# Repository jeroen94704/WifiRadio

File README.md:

WifiRadio
=========

Introduction
------------

This is the software part of my version of the ubiquitous wifi radio projects. There are many similar builds to be found online, 
and they all use a cheap router as an internet streaming radio, usually running MPD (http://mpd.wikia.com/wiki/Music_Player_Daemon_Wiki) 
to play the music. My build borrows heavily from the radio project by Jeff Keyzer, A.K.A. MightyOhm. He documented the process he 
went through in great detail on his blog, at http://mightyohm.com/blog/2008/10/building-a-wifi-radio-part-1-introduction/

In addition, I also owe a great deal to the SparkFun tutorial "Beginning embedded electronics", which can be found at 
http://www.sparkfun.com/tutorials/57

Contents
--------

The repository contains the following:

* C-code, to be compiled and programmed onto a suitable AVR microcontroller
* A perl script, which runs on the router
* Eagle schematics and board files of the electronics

Features
--------

The firmware+perl script system has the following features:

* Load a predefined playlist containing a set of internet streams
* Browse and play from an MP3 collection located on a network share
* Show currently playing information, including progress in the current track, title/artist info and playlist info

Usage
-----

The player is controlled using a 6-button keypad, with up/down/left/right/enter keys, and a mode switch key. The player starts in radio mode, 
playing the predefined set of internet streams. Pressing the mode switch key will start the MP3 browser mode, and shows the first few MP3 directories 
(in my case, artists). The browser is fully file based, so ID3 tags inside the MP3's are not interpreted. Use up/down to move through the list, press 
"right" to enter a directory, and show what's inside. Press "left" to go up one directory level. Press "enter" to play the currently selected item. If
this is a directory, everything inside that directory and its subdirectories will be played. Pressing the mode switch button again will reload and play
the predefined internet streams once more.

While playing, left/right let you move through the playlist, while up/down controls the volume (not shown on the display).
	
Technical details
-----------------
	
### C-Code

The code was built using the WinAVR suite of tools. You can use the included makefile to build your own binary, which includes targets to set the fuses and program the MPU.

### Perl script

This is a firm departure from Jeff's build, which uses bash scripting to do all the router-side processing. Since I need fairly elaborate two-way communication, involving
a lot of string parsing, using Perl with its built-in regex support was a logical move. The code is a bit dirty in the way it handles 2-way requests (e.g. When the AVR 
asks for a list of tracks). These requests involve receiving a message, processing it, and sending a result back to the AVR. The script forks at startup, so the receiving
and sending parts run in different processes.

When a results needs to be returned to the AVR, the receiver process writes a file containing the response. The sender process detects the existance if this file, reads it, 
sends the data over the serial line, and removes the file. 

More investigation is needed to determine whether the fork is actually necessary. An alternative would be to move to C, and use a proper multithreading approach, but I've 
cracked my skull against setting up an OpenWrt toolchain in the past, and have no immediate desire to attempt this again, also since the current implementation works just fine.

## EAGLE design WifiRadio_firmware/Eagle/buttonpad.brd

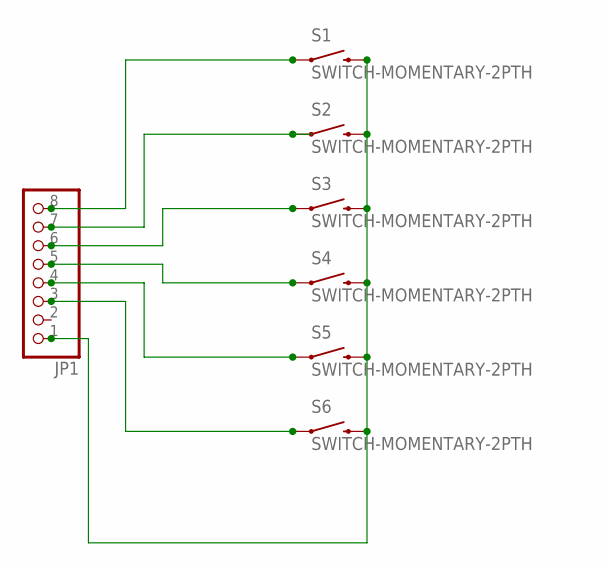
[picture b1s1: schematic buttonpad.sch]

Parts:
JP1: PINHD-1X8; 1X08
S1, S2, S3, S4, S5, S6: SWITCH-MOMENTARY-2PTH; TACTILE-PTH

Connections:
GND: JP1.1, S1.3 (2), S2.3 (2), S3.3 (2), S4.3 (2), S5.3 (2), S6.3 (2)
unnamed: JP1.8, S1.1
unnamed: JP1.6, S3.1
unnamed: JP1.3, S6.1
unnamed: JP1.7, S2.1
unnamed: JP1.5, S4.1
unnamed: JP1.4, S5.1

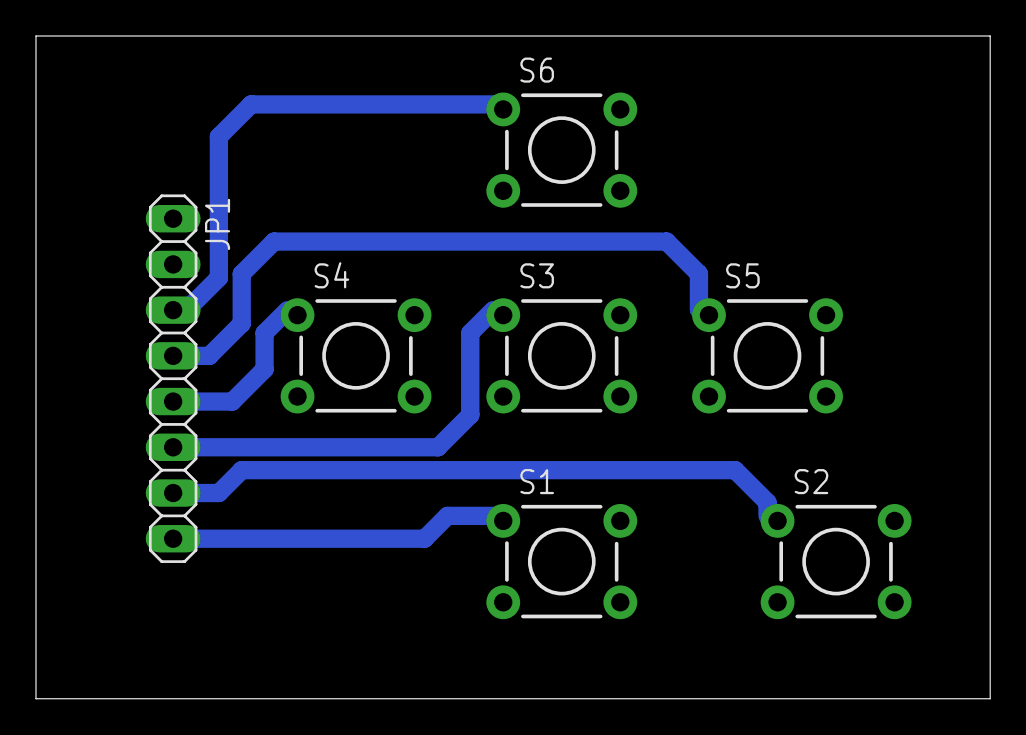
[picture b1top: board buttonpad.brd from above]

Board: 2 copper layers, 53.0 x 36.8 mm, 7 parts (0 on the bottom side), 7 nets.

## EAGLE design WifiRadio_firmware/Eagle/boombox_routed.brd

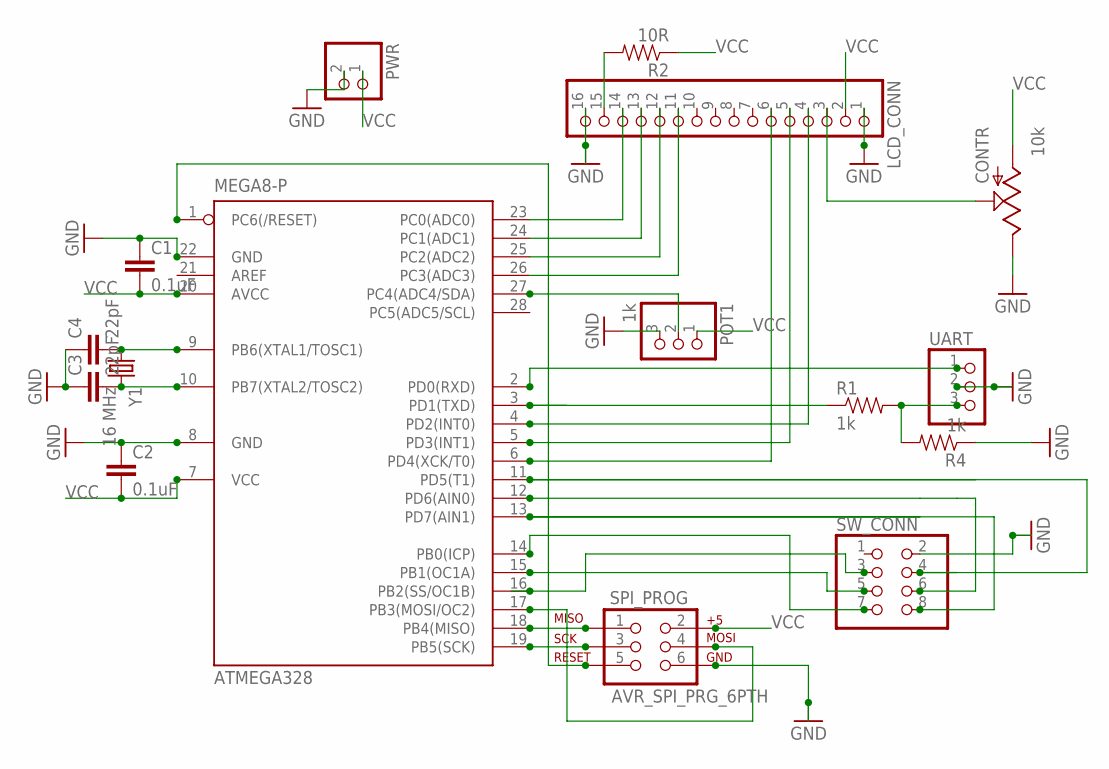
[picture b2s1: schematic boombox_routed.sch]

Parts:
ATMEGA328: MEGA8-P; DIL28-3
C1, C2: 0.1uF; C2.5-2
C3, C4: 22pF; C2.5-2
CONTR: 10k; 3362U
LCD_CONN: PINHD-1X16; 1X16
POT1: 1k; 1X03
PWR: PINHD-1X2; 1X02
R1, R4: 1k; AXIAL-0.4
R2: 10R; AXIAL-0.4
SPI_PROG: AVR_SPI_PRG_6PTH; 2X3
SW_CONN: PINHD-2X4; 2X04
UART: PINHD-1X3; 1X03
Y1: 16 MHz; HC49US

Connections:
GND: ATMEGA328.8 (GND), ATMEGA328.22 (GND), C1.1, C2.1, C3.1, C4.1, CONTR.P$1 (E), LCD_CONN.1, LCD_CONN.16, POT1.3, PWR.2, R4.P$1 (1), SPI_PROG.6, SW_CONN.1, SW_CONN.2, UART.2; also elsewhere on the board
unnamed: ATMEGA328.10 (PB7(XTAL2/TOSC2)), C3.2, Y1.2
unnamed: ATMEGA328.9 (PB6(XTAL1/TOSC1)), C4.2, Y1.1
unnamed: CONTR.P$2 (S), LCD_CONN.3
unnamed: ATMEGA328.3 (PD1(TXD)), R1.P$1 (1)
unnamed: R1.P$2 (2), R4.P$2 (2), UART.3
unnamed: ATMEGA328.2 (PD0(RXD)), UART.1
unnamed: ATMEGA328.4 (PD2(INT0)), LCD_CONN.4
unnamed: ATMEGA328.5 (PD3(INT1)), LCD_CONN.5
unnamed: ATMEGA328.6 (PD4(XCK/T0)), LCD_CONN.6
unnamed: LCD_CONN.15, R2.P$2 (2)
unnamed: ATMEGA328.23 (PC0(ADC0)), LCD_CONN.14
unnamed: ATMEGA328.24 (PC1(ADC1)), LCD_CONN.13
unnamed: ATMEGA328.25 (PC2(ADC2)), LCD_CONN.12
unnamed: ATMEGA328.26 (PC3(ADC3)), LCD_CONN.11
unnamed: ATMEGA328.19 (PB5(SCK)), SPI_PROG.3
unnamed: ATMEGA328.18 (PB4(MISO)), SPI_PROG.1
unnamed: ATMEGA328.17 (PB3(MOSI/OC2)), SPI_PROG.4
unnamed: ATMEGA328.14 (PB0(ICP)), SW_CONN.7
unnamed: ATMEGA328.27 (PC4(ADC4/SDA)), POT1.2
unnamed: ATMEGA328.15 (PB1(OC1A)), SW_CONN.5
unnamed: ATMEGA328.12 (PD6(AIN0)), SW_CONN.6
unnamed: ATMEGA328.13 (PD7(AIN1)), SW_CONN.8
unnamed: ATMEGA328.11 (PD5(T1)), SW_CONN.4
unnamed: ATMEGA328.16 (PB2(SS/OC1B)), SW_CONN.3
unnamed: ATMEGA328.1 (PC6(/RESET)), SPI_PROG.5
VCC: ATMEGA328.7 (VCC), ATMEGA328.20 (AVCC), C1.2, C2.2, CONTR.P$3 (A), LCD_CONN.2, POT1.1, PWR.1, R2.P$1 (1), SPI_PROG.2; also elsewhere on the board

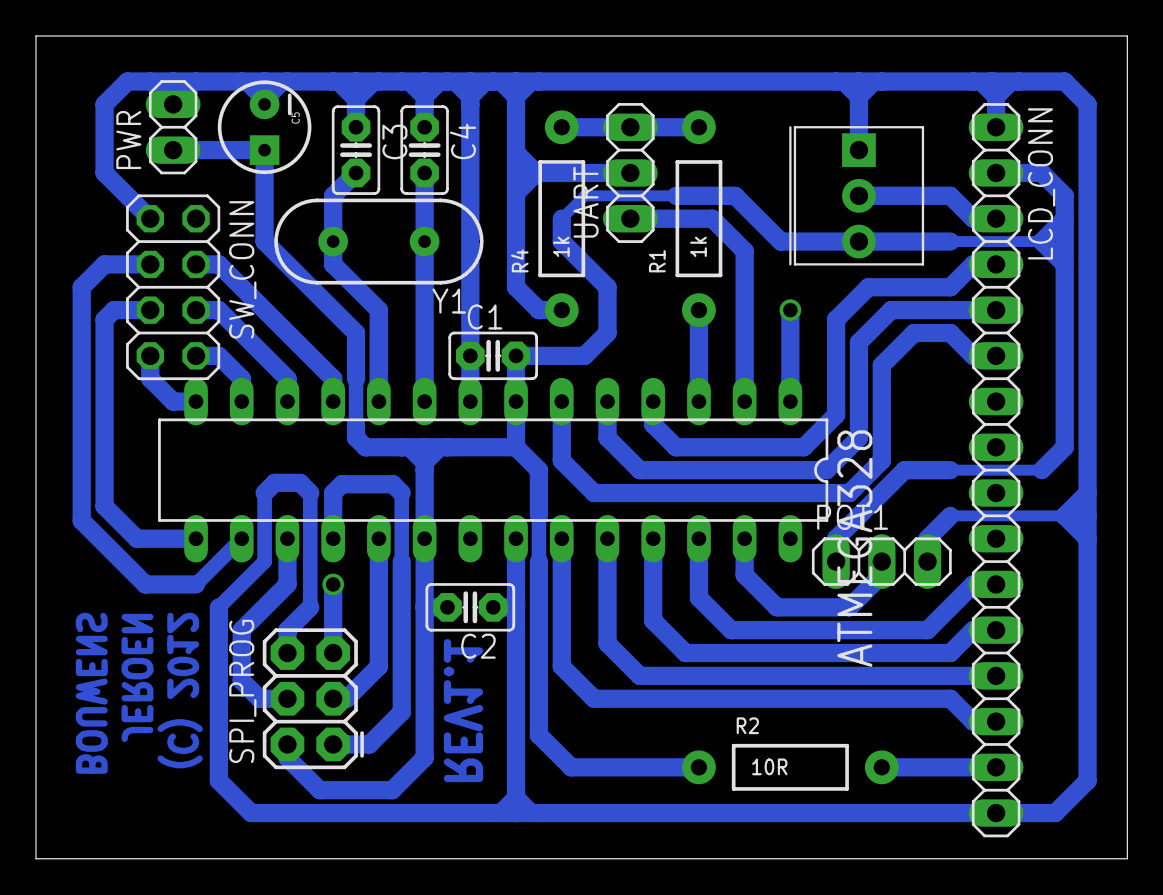
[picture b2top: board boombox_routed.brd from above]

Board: 2 copper layers, 60.6 x 45.7 mm, 17 parts (0 on the bottom side), 27 nets.

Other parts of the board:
C5: 10uF; CPOL-RADIAL-10UF-25V

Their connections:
GND: C5.2; also elsewhere on the board
VCC: C5.1; also elsewhere on the board

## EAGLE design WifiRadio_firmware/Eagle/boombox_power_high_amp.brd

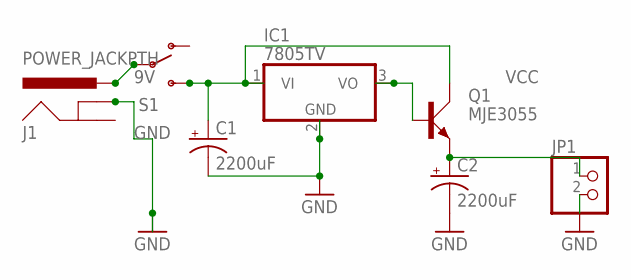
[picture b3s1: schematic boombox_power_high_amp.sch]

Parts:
C1, C2: 2200uF; CPOL-RADIAL-1000UF-25V
IC1: 7805TV; TO220V
J1: POWER_JACKPTH; POWER_JACK_PTH
JP1: PINHD-1X2; 1X02
Q1: MJE3055; TO220AV
S1: SWITCH-SPSTPTH; SWITCH-SPDT

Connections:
9V: C1.1 (+), IC1.1 (VI), Q1.C, S1.3 (S)
GND: C1.2 (-), C2.2 (-), IC1.2 (GND), J1.GNDBREAK, JP1.2
unnamed: J1.PWR, S1.2
unnamed: C2.1 (+), JP1.1, Q1.E
VCC: IC1.3 (VO), Q1.B

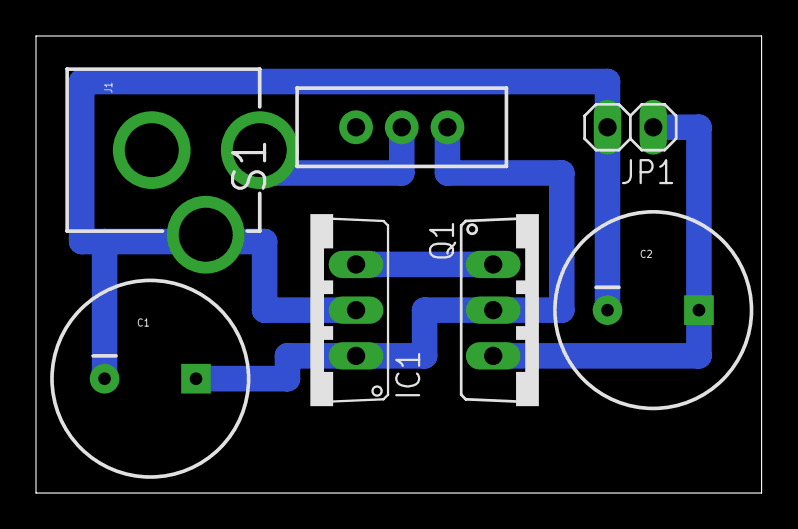
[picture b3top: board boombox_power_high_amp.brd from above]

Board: 2 copper layers, 40.3 x 25.4 mm, 7 parts (0 on the bottom side), 5 nets.

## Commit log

2011-11-24 Init of the repo, added all files
2011-12-19 Trying to get bidirectional serial comms working.
2011-12-22 Added second button (now used to reload the standard playlist).
2011-12-29 Started implementation of track browser
2012-01-27 Started implementation of browsing functionality
2012-01-28 First working version of mp3 browsing. Also added router-side perl script
2012-01-28 Added comments
2012-01-29 Added eagle design files
2012-01-30 Fixed DRC warnings
2012-01-31 Finished manual routing
2012-01-31 Modified everything to avoid 90 degree angles
2012-01-31 Fixed small error
2012-01-31 More angle changes
2012-01-31 some small changes
2012-02-01 Added back the 10 uF stabilizing cap
2012-02-10 Added schematics for a buttonpad and display gender changer.
2012-02-17 Modified boards, changed pin asignment in lcd driver
2012-02-17 Removed obsolete files
2012-02-17 Removed unused files
2012-02-17 Added readme for github
2012-02-17 Added usage instructions
2012-02-18 Indentation change
2012-04-02 Added file
2012-09-27 Added shark project '
2012-09-27 bidirectional communication works. winode broadcasts values, and nanode can set values
2012-10-30 Removed files from the Shark project
2012-10-30 Removed Jenkins monitor files

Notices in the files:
WifiRadio_firmware/Eagle/boombox_routed.brd:
(C) 2012
parts and their libraries:
SparkFun: Licensing: CC v3.0 Share-Alike You are welcome to use this library for commercial purposes.
